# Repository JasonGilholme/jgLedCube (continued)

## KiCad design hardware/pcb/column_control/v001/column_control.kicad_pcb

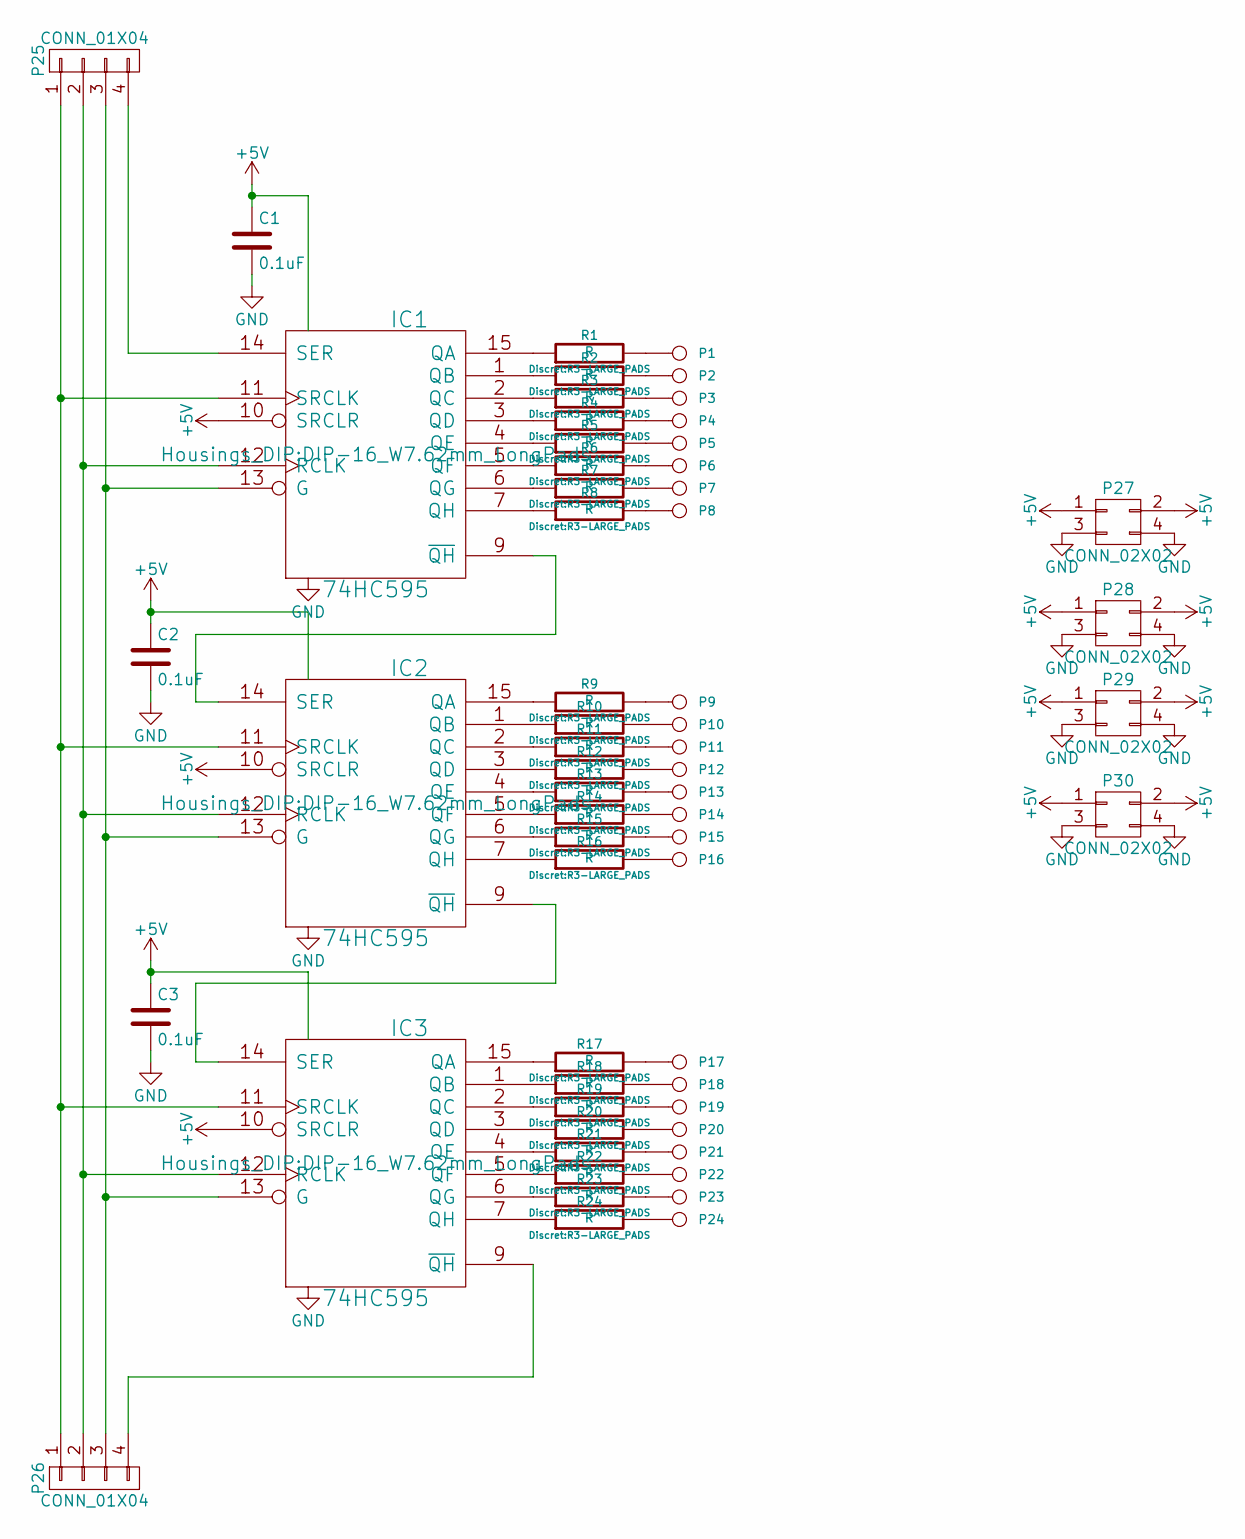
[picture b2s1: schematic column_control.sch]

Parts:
C1, C2, C3: 0.1uF; C_Disc_D3_P2.5
IC1, IC2, IC3: 74HC595; DIP-16_W7.62mm_LongPads
P1, P2, P3, P4, P5, P6, P7, P8, P9, P10, P11, P12, P13, P14, P15, P16, P17, P18, P19, P20, P21, P22, P23, P24: CONN_1; Socket_Strip_Straight_1x01
P25, P26: CONN_01X04; Socket_Strip_Straight_1x04
P27, P28, P29, P30: CONN_02X02; Socket_Strip_Straight_2x02
R1, R2, R3, R4, R5, R6, R7, R8, R9, R10, R11, R12, R13, R14, R15, R16, R17, R18, R19, R20, R21, R22, R23, R24: R; R3-LARGE_PADS

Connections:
+5V: C1.1, C2.1, C3.1, IC1.10 (SRCLR), IC1.16 (VCC), IC2.10 (SRCLR), IC2.16 (VCC), IC3.10 (SRCLR), IC3.16 (VCC), P27.1, P27.2, P28.1, P28.2, P29.1, P29.2, P30.1, P30.2
GND: C1.2, C2.2, C3.2, IC1.8 (GND), IC2.8 (GND), IC3.8 (GND), P27.3, P27.4, P28.3, P28.4, P29.3, P29.4, P30.3, P30.4
unnamed: IC1.1 (QB), R2.1
unnamed: IC1.2 (QC), R3.1
unnamed: IC1.3 (QD), R4.1
unnamed: IC1.4 (QE), R5.1
unnamed: IC1.5 (QF), R6.1
unnamed: IC1.6 (QG), R7.1
unnamed: IC1.7 (QH), R8.1
unnamed: IC1.9 (~QH), IC2.14 (SER)
unnamed: IC1.11 (SRCLK), IC2.11 (SRCLK), IC3.11 (SRCLK), P25.1, P26.1
unnamed: IC1.12 (RCLK), IC2.12 (RCLK), IC3.12 (RCLK), P25.2, P26.2
unnamed: IC1.13 (G), IC2.13 (G), IC3.13 (G), P25.3, P26.3
unnamed: IC1.14 (SER), P25.4
unnamed: IC1.15 (QA), R1.1
unnamed: IC2.1 (QB), R10.1
unnamed: IC2.2 (QC), R11.1
unnamed: IC2.3 (QD), R12.1
unnamed: IC2.4 (QE), R13.1
unnamed: IC2.5 (QF), R14.1
unnamed: IC2.6 (QG), R15.1
unnamed: IC2.7 (QH), R16.1
unnamed: IC2.9 (~QH), IC3.14 (SER)
unnamed: IC2.15 (QA), R9.1
unnamed: IC3.1 (QB), R18.1
unnamed: IC3.2 (QC), R19.1
unnamed: IC3.3 (QD), R20.1
unnamed: IC3.4 (QE), R21.1
unnamed: IC3.5 (QF), R22.1
unnamed: IC3.6 (QG), R23.1
unnamed: IC3.7 (QH), R24.1
unnamed: IC3.9 (~QH), P26.4
unnamed: IC3.15 (QA), R17.1
unnamed: P1.1, R1.2
unnamed: P2.1, R2.2
unnamed: P3.1, R3.2
unnamed: P4.1, R4.2
unnamed: P5.1, R5.2
unnamed: P6.1, R6.2
unnamed: P7.1, R7.2
unnamed: P8.1, R8.2
unnamed: P9.1, R9.2
unnamed: P10.1, R10.2
unnamed: P11.1, R11.2
unnamed: P12.1, R12.2
unnamed: P13.1, R13.2
unnamed: P14.1, R14.2
unnamed: P15.1, R15.2
unnamed: P16.1, R16.2
unnamed: P17.1, R17.2
unnamed: P18.1, R18.2
unnamed: P19.1, R19.2
unnamed: P20.1, R20.2
unnamed: P21.1, R21.2
unnamed: P22.1, R22.2
unnamed: P23.1, R23.2
unnamed: P24.1, R24.2

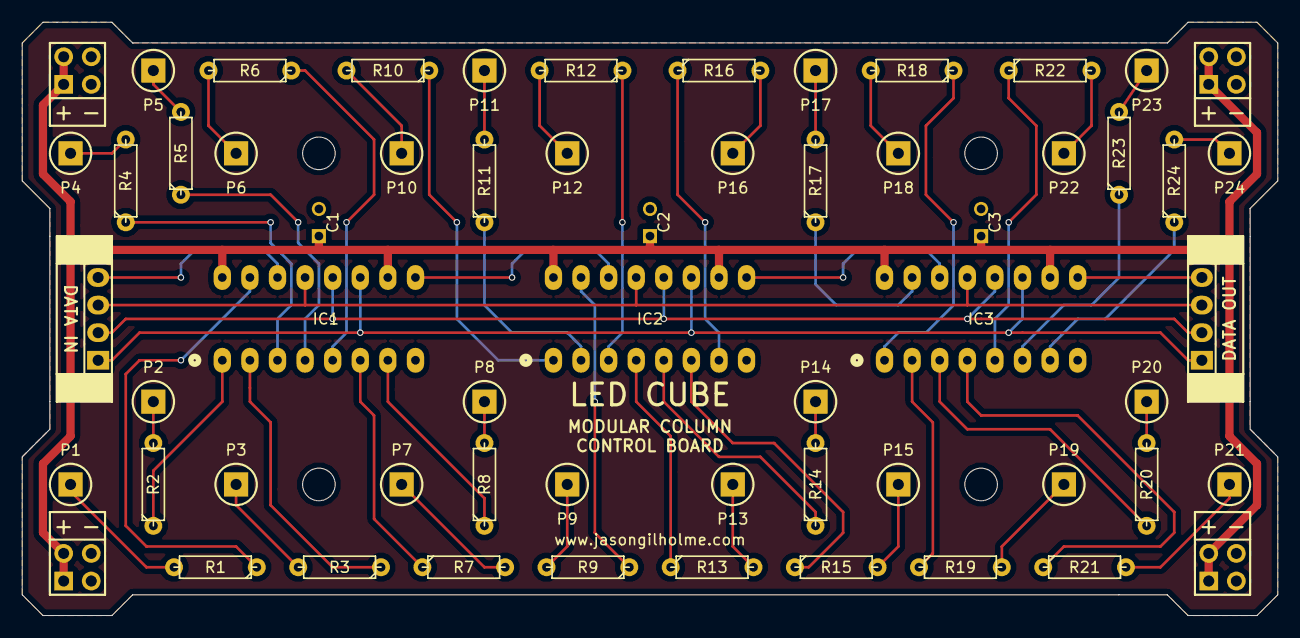
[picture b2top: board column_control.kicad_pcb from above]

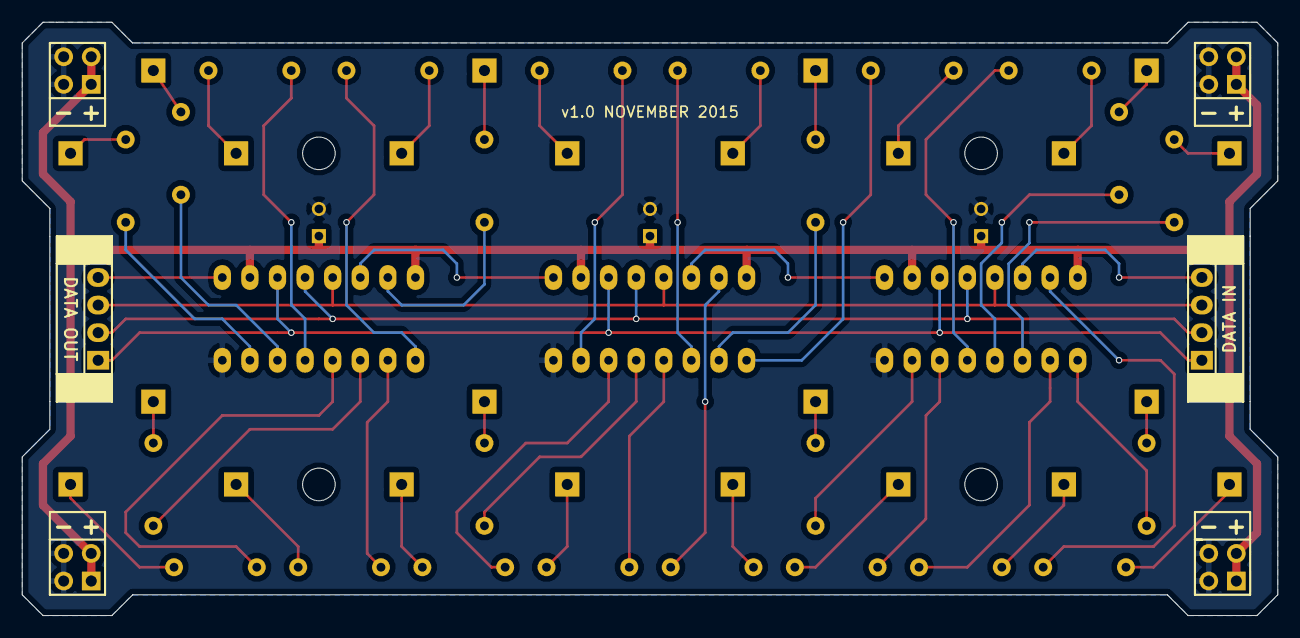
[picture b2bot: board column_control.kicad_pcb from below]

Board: 2 copper layers, 115.6 x 54.6 mm, 60 parts (6 on the bottom side), 57 nets.

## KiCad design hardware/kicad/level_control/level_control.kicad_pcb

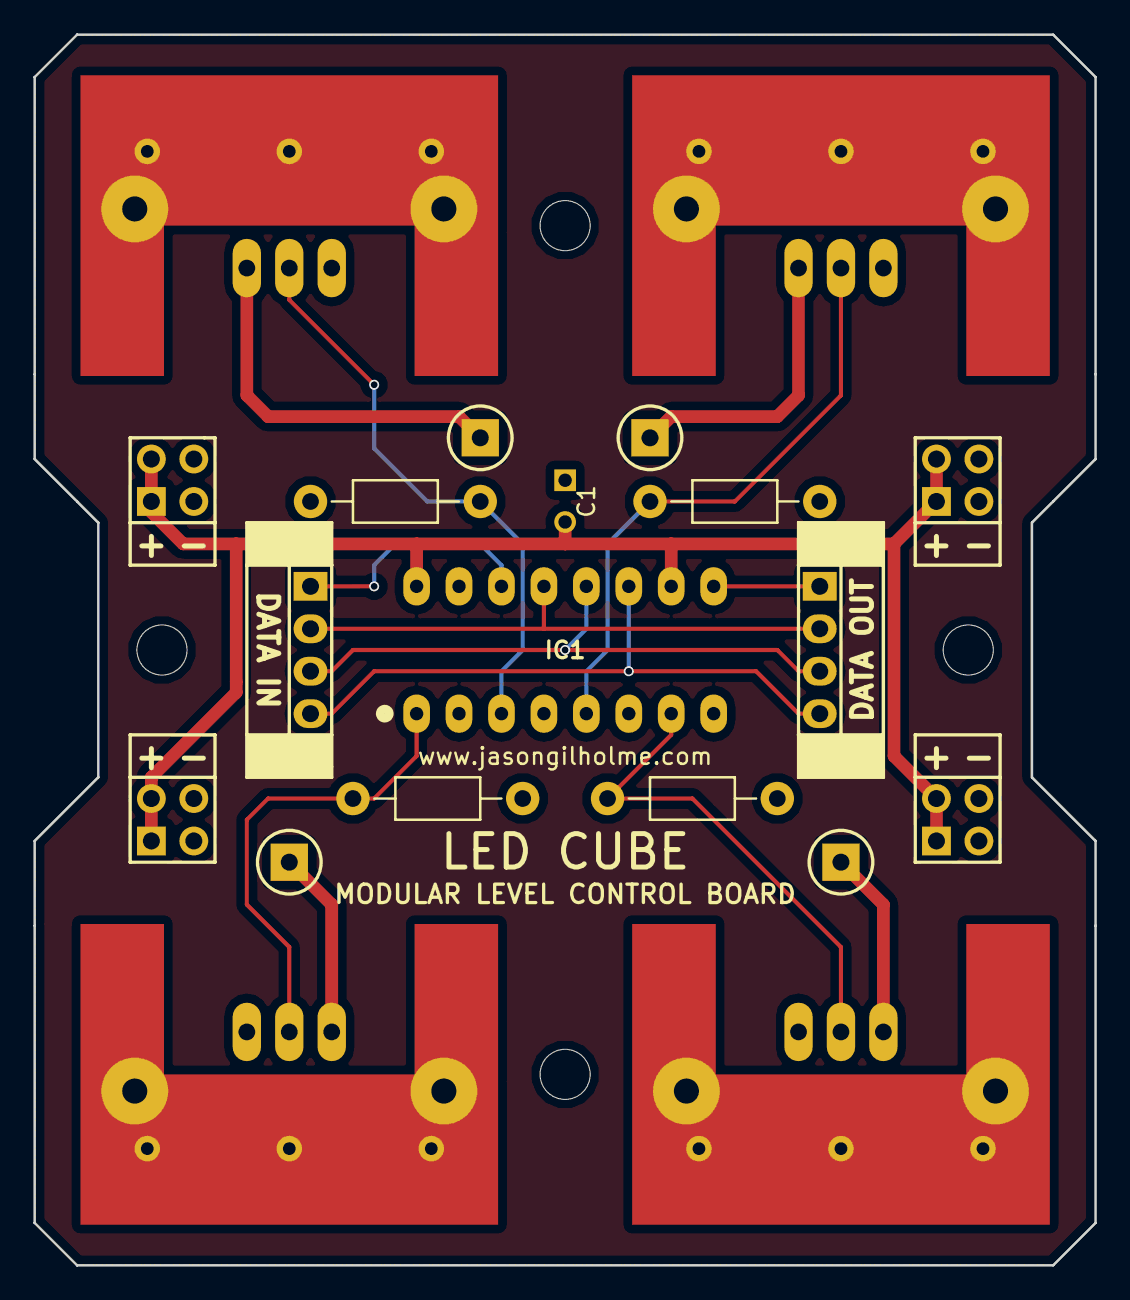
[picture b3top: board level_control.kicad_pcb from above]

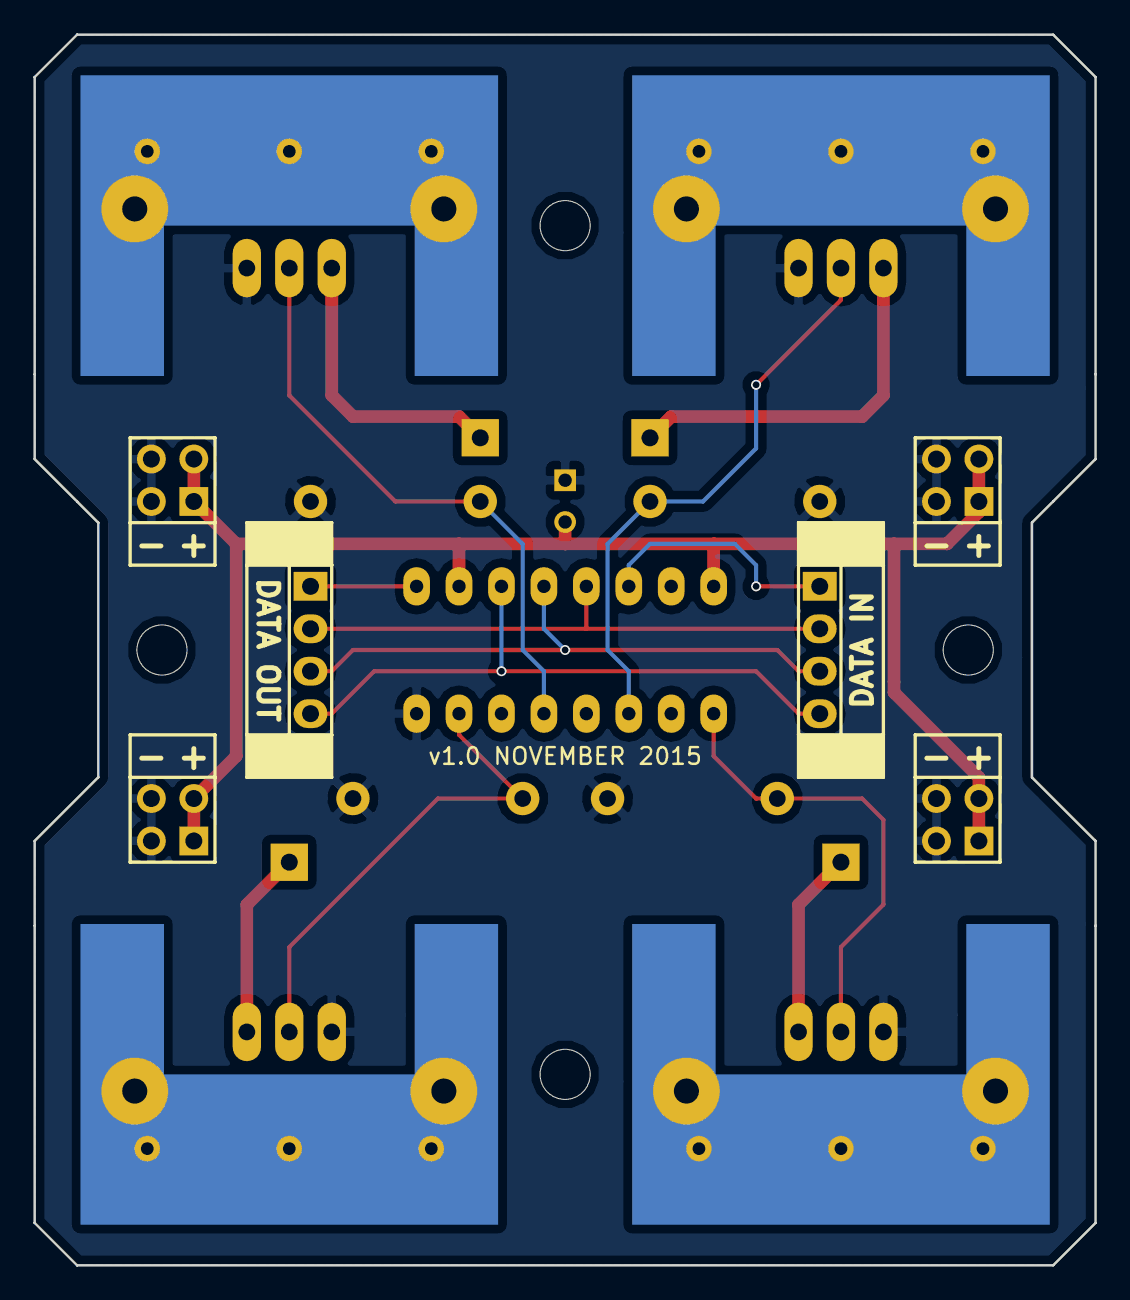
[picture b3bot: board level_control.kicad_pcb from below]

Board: 2 copper layers, 63.5 x 73.7 mm, 24 parts (6 on the bottom side), 15 nets.

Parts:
C1: 0.1uF; C_Disc_D3_P2.5
HS1, HS2, HS3, HS4: HEATSINK_JASE; HeatsinkWithExposedCopper
P1: LEVEL_1; Socket_Strip_Straight_1x01
P2: LEVEL_2; Socket_Strip_Straight_1x01
P3: LEVEL_3; Socket_Strip_Straight_1x01
P4: LEVEL_4; Socket_Strip_Straight_1x01
P5, P6: CONN_01X04; Socket_Strip_Straight_1x04
P7, P8, P9, P10: CONN_02X02; Socket_Strip_Straight_2x02
Q1, Q2, Q3, Q4: BUZ11; TO-220_Neutral123_Vertical_LargePads
R1, R2, R3, R4: 10k; Resistor_Horizontal_RM10mm
U1: 74HC595; DIP-16_W7.62mm_LongPads

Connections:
+5V: C1.2, P7.1, P7.2, P8.1, P8.2, P9.1, P9.2, P10.1, P10.2, U1.10, U1.16
GND: C1.1, P7.3, P7.4, P8.3, P8.4, P9.3, P9.4, P10.3, P10.4, Q1.3, Q2.3, Q3.3, Q4.3, R1.1, R2.1, R3.1, R4.1, U1.8
unnamed: P1.1, Q1.1
unnamed: P2.1, Q2.1
unnamed: P3.1, Q3.1
unnamed: P4.1, Q4.1
unnamed: P5.1, U1.14
unnamed: P5.2, P6.2, U1.13
unnamed: P5.3, P6.3, U1.12
unnamed: P5.4, P6.4, U1.11
unnamed: P6.1, U1.9
unnamed: Q1.2, R1.2, U1.1
unnamed: Q2.2, R2.2, U1.3
unnamed: Q3.2, R3.2, U1.5
unnamed: Q4.2, R4.2, U1.7

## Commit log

2016-09-27 Initial commit of core lib and some tests.
2016-09-27 clear() & first pass on setLed().
2016-09-27 Prototypes for anim and serial modules, namespaces and code stubs.
2016-09-29 Started to setup the build system to be able to build to different target hardware.
2016-09-29 setLed() implemented
2016-09-29 Added STM32 cmake toolchain. Using the preprocessor for calculating constant values.
2016-09-30 Cube identifier constants.
2016-09-30 n_colors bug, renamed test dir to pc to fulfill the hardware platform concept
2016-09-30 extern const declare in .h and const definition in .cpp. Otherwise I get duplicate objects, one external for everything and one internal to the cpp
2016-09-30 Bug fix when identifying correct byte & bit in setLed(). Using uint16 to cater for 8x8x8 cubes. Working tests.
2016-09-30 Debug output for troubleshooting.
2016-09-30 moarrrrr output
2016-09-30 Fixed arduino linking bug. Re-structure cmake to reflect the new requirements
2016-09-30 removing some temp debug data.
2016-10-01 Started the animation libraries.
2016-10-01 Debug anim clean up
2016-10-01 Sweep anim
2016-10-01 Added core::getLed()
2016-10-01 Added anim::fade_out
2016-10-01 travis?
2016-10-01 reduced cmake required version
2016-10-01 install gtest before building
2016-10-01 verbose make for debug
2016-10-01 travis: compile with c++ not g++ ??
2016-10-01 type casting in tests.
2016-10-01 install gtest before building - dev and libs
2016-10-01 travis - gotta build the gtest lib from src.
2016-10-01 still travising
2016-10-01 running tests on travis - commented out segfaulting tests for the moment.
2016-10-01 crossing the streams on travis
2016-10-01 full path to avr compiler for travis - prefer to set PATH
2016-10-01 travis: Added to PATH env var, and install arduino libs.
2016-10-01 travis: different bash test for PC built target. Expanded gtest build string for readability.
2016-10-01 travis: Removed compiler cline flag
2016-10-01 Added BuildStatus to readme.
2016-10-01 travis formatting
2016-10-01 travis: build from a build sub dir
2016-10-02 Started implemented some serial comms logic.
2016-10-02 Added serial lib for arduino builds
2016-10-02 Added testing of command id and fixed a broken one. tdd!
2016-10-02 Serial: added getConfig funcs.
2016-10-02 Added more thorough getLed() test.
2016-10-02 Serial support for clear(), getConfig() and process(). Separated encoding and processing tests.
2016-10-02 static vars for high frequency funcs.
2016-10-03 Serial Transport with boost on pc.
2016-10-03 Serial lib uses serial_pc.cpp & links to boost_system
2016-10-03 Travis: added boost
2016-10-03 Travis: added boost - no typo this time.
2016-10-03 Added PHONY_SERIAL option for testing purposes.
2016-10-04 Restructured repo
2016-10-04 travis
2016-10-04 travis: chmod +x
2016-10-04 travis: script pathing
2016-10-04 includes
2016-10-06 Serial send/receive + tests. anim include bug fix.
2016-10-06 different init for serial port
2016-10-06 hardware specific serial lib build support.
2016-10-07 Added core::redraw() and core::flood()
2016-10-07 Changed getters/setters to match the hardware configuration.
2016-10-07 statics
2016-10-07 started Python bindings for serial command lib
2016-10-07 travis: added python-dev for desktop builds
2016-10-07 cmake: using find_package for boost and python.
2016-10-07 cmake: project() being run in some weird places.
2016-10-08 More python bindings. Added install targets. Python tests during travis build.
2016-10-08 Finding Python 2.7, only making python libs when not doing any embedded build.
2016-10-08 better python test verbosity
2016-10-08 travis: clang?
2016-10-08 renamed python test case
2016-10-08 Better use of find_package results. Hooks for android toolchain.
2016-10-08 travis: clang not installed?
2016-10-15 Blender files for jigs
2016-10-17 Hardware source files and some images
2016-10-17 Readme updates
2016-10-17 readme - html header?
2016-10-17 resize image
2016-10-21 added some hardware docs - preparing for v2 pcb design
2016-10-21 removed .idea files
2016-10-21 added ignore file for .idea dir
2016-10-21 scope rnd on transistor switching
2016-10-22 Added more scope images and some notes
2016-10-22 high side switch rnd
2016-10-30 Added switch array kicad project
2016-10-30 Added pcb pdf
2016-10-30 high side switch array: correct 595 ic wiring
2017-01-28 Set theme jekyll-theme-architect
2017-03-04 restructuring
2017-03-05 started playing around with qt for a desktop controller ui.
2017-03-05 added missing ui file. added a rez env shell script to get the dev environment
2017-03-05 qt5 for travis ci build env
2017-03-05 Minimum req of Qt5.2 to allow building with qt from ubuntu 16 ppa
2017-03-05 travis ci - trying with qtserialport5-dbg
2017-03-05 ui revisions and laid out sysmon controls.
2017-04-01 more restructuring
2017-04-02 Logic for connected cube discovery
2017-04-02 Setup catch testing alongside gtests.
2017-04-02 common/desktop: removed redundant source file
2017-04-02 moved data into jgLedCube/cubes dir. Added in boost.python wrap of serial comms.
2017-04-02 linking python wrapper to correct lib.
